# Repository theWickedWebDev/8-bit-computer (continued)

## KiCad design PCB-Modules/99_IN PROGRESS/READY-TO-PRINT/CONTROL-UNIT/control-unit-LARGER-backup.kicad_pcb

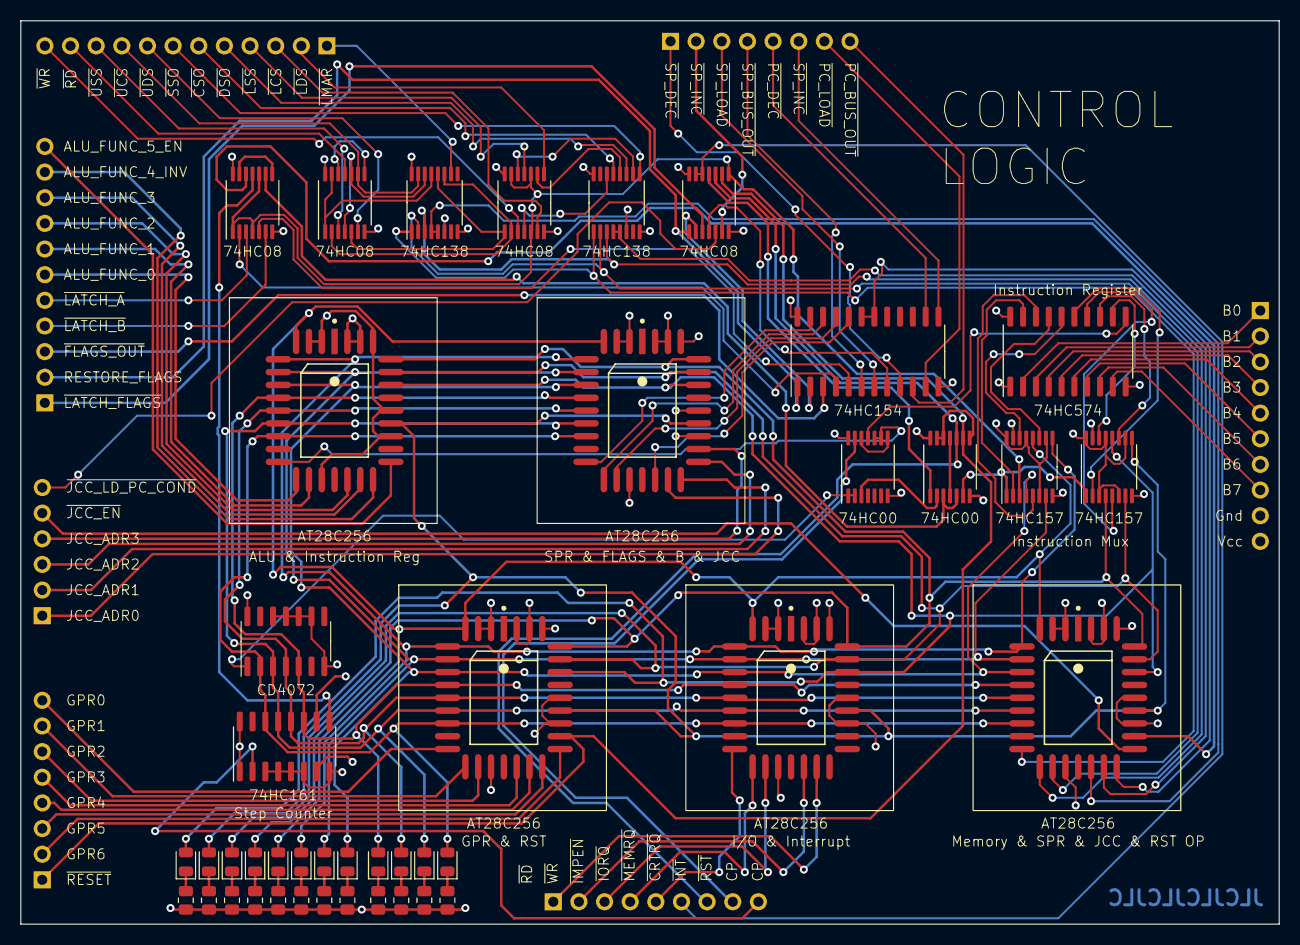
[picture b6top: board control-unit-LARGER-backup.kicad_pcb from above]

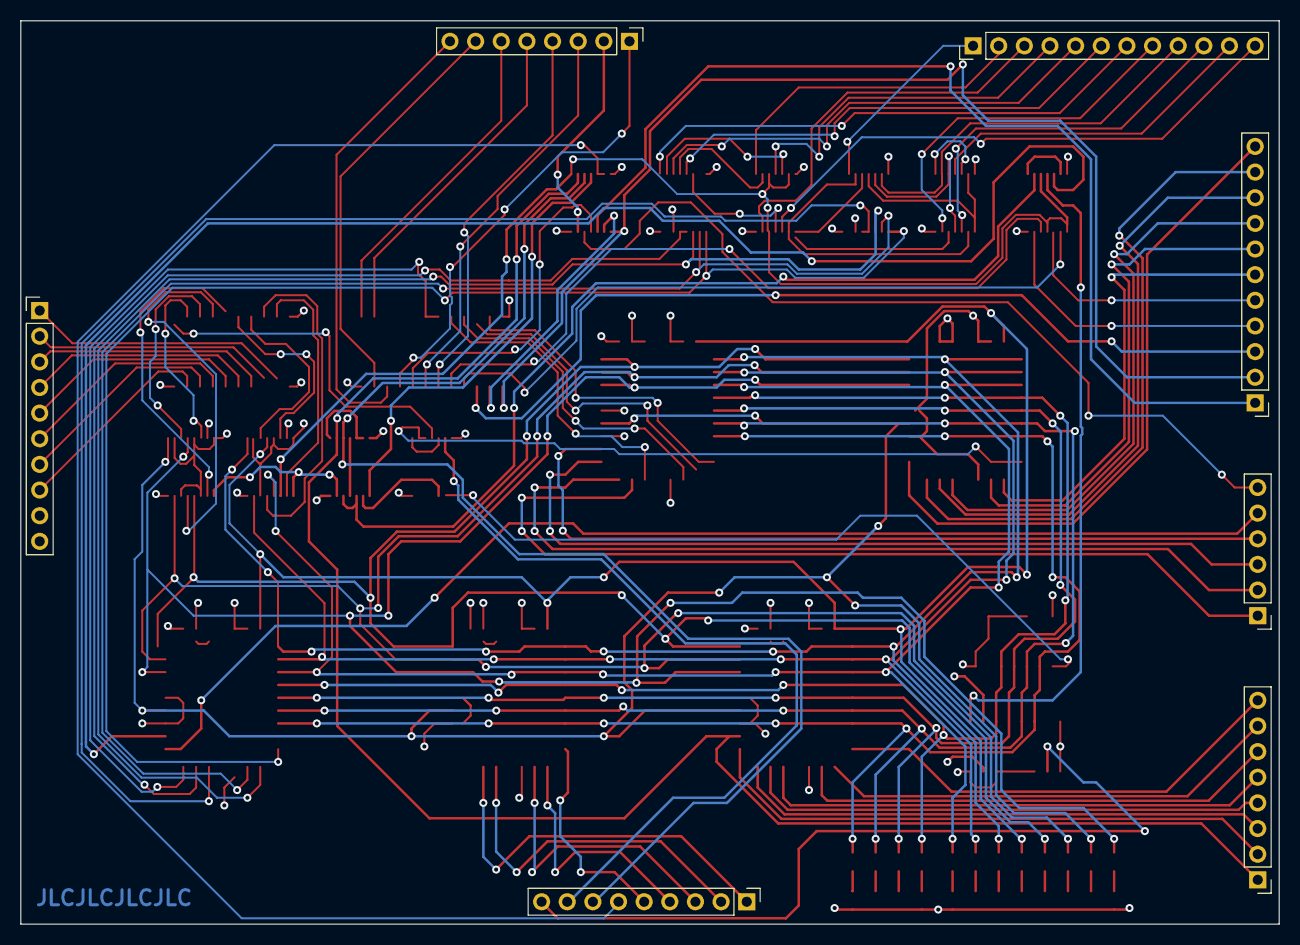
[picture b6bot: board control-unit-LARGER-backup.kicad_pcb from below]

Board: 4 copper layers, 124.6 x 89.5 mm, 50 parts (7 on the bottom side), 132 nets.

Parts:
D1, D2, D3, D4, D5, D6, D7, D8, D9, D10, D11, D12: LED; LED_0805_2012Metric
J1: Conn_01x09; PinHeader_1x09_P2.54mm_Vertical
J2, J7: Conn_01x08; PinHeader_1x08_P2.54mm_Vertical
J3: Conn_01x11; PinHeader_1x11_P2.54mm_Vertical
J4: Conn_01x10; PinHeader_1x10_P2.54mm_Vertical
J5: Conn_01x06; PinHeader_1x06_P2.54mm_Vertical
J6: Conn_01x12; PinHeader_1x12_P2.54mm_Vertical
R1, R2, R3, R4, R5, R6, R7, R8, R9, R10, R11, R12: R_US; R_0805_2012Metric
U1: 74LS161; SOIC-16_3.9x9.9mm_P1.27mm
U2: 4072; SOIC-14_3.9x8.7mm_P1.27mm
U3, U5: 74LS157; TSSOP-16_4.4x5mm_P0.65mm
U4, U19: 74LS00; TSSOP-14_4.4x5mm_P0.65mm
U6, U11, U12, U14, U15: PLCC32_28_28C256; Microchip-32J-10_2001-B-IPC_A
U7, U13: 74LS138; TSSOP-16_4.4x5mm_P0.65mm
U8: 74LS154; SO-24_5.3x15mm_P1.27mm
U9, U10, U16, U17: 74LS08; TSSOP-14_4.4x5mm_P0.65mm
U18: 74LS574; SO-20_5.3x12.6mm_P1.27mm

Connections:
/~RD_DATA: U7.14 (O1), U9.4, U9.10
/~RD_STACK: U7.13 (O2), U9.1, U9.13
/~WR_DATA: U7.12 (O3), U9.5, U17.1
/~WR_STACK: U7.11 (O4), U9.2, U17.2
ALU_FUNC_0: J3.6, U12.14 (I/O1)
ALU_FUNC_1: J3.7, U12.15 (I/O2)
ALU_FUNC_2: J3.8, U12.18 (I/O3)
ALU_FUNC_3: J3.9, U12.19 (I/O4)
ALU_FUNC_4: J3.10, U12.20 (I/O5)
ALU_FUNC_5_EN: J3.11, U12.21 (I/O6)
BUS0: J4.1, U18.2 (D0)
BUS1: J4.2, U18.3 (D1)
BUS2: J4.3, U18.4 (D2)
BUS3: J4.4, U18.5 (D3)
BUS4: J4.5, U18.6 (D4)
BUS5: J4.6, U18.7 (D5)
BUS6: J4.7, U18.8 (D6)
BUS7: J4.8, U18.9 (D7)
CLOCK: J1.8, U4.13
GND: J4.9, R1.2, R2.2, R3.2, R4.2, R5.2, R6.2, R7.2, R8.2, R9.2, R10.2, R11.2, R12.2, U1.3 (D0), U1.4 (D1), U1.5 (D2), U1.6 (D3), U1.8 (GND), U2.7 (VSS), U2.9, U2.10, U2.11, U2.12, U3.8 (GND), U3.15 (E), U4.7 (GND), U5.8 (GND), U5.15 (E), U6.2 (A14), U6.3 (A12), U6.16 (Gnd), U6.23 (~CE), U6.25 (~OE), U6.30 (A14), U7.8 (GND), U8.12 (GND), U9.7 (GND), U10.7 (GND), U11.2 (A14), U11.3 (A12), U11.16 (Gnd), U11.23 (~CE), U11.25 (~OE), U11.30 (A14), U12.2 (A14), U12.3 (A12), U12.16 (Gnd), U12.23 (~CE), U12.25 (~OE), U12.30 (A14), U13.8 (GND), U14.2 (A14), U14.3 (A12), U14.16 (Gnd), U14.23 (~CE), U14.25 (~OE), U14.30 (A14), U15.2 (A14), U15.3 (A12), U15.16 (Gnd), U15.23 (~CE), U15.25 (~OE), U15.30 (A14), U16.7 (GND), U17.7 (GND), U18.1 (OE), U18.10 (GND), U19.7 (GND)
GPR0: J2.8, U11.13 (I/O0)
GPR1: J2.7, U11.14 (I/O1)
GPR2: J2.6, U11.15 (I/O2)
GPR3: J2.5, U11.18 (I/O3)
GPR4: J2.4, U11.19 (I/O4)
GPR5: J2.3, U11.20 (I/O5)
GPR6: J2.2, U11.21 (I/O6)
INST0: D12.2 (A), U3.4 (Za), U6.7 (A4), U11.7 (A4), U12.7 (A4), U14.7 (A4), U15.7 (A4)
INST1: D11.2 (A), U3.7 (Zb), U6.6 (A5), U11.6 (A5), U12.6 (A5), U14.6 (A5), U15.6 (A5)
INST2: D10.2 (A), U3.9 (Zc), U6.5 (A6), U11.5 (A6), U12.5 (A6), U14.5 (A6), U15.5 (A6)
INST3: D9.2 (A), U3.12 (Zd), U6.4 (A7), U11.4 (A7), U12.4 (A7), U14.4 (A7), U15.4 (A7)
INST4: D8.2 (A), U5.4 (Za), U6.29 (A8), U11.29 (A8), U12.29 (A8), U14.29 (A8), U15.29 (A8)
INST5: D7.2 (A), U5.7 (Zb), U6.28 (A9), U11.28 (A9), U12.28 (A9), U14.28 (A9), U15.28 (A9)
INST6: D6.2 (A), U5.9 (Zc), U6.24 (A10), U11.24 (A10), U12.24 (A10), U14.24 (A10), U15.24 (A10)
INST7: D5.2 (A), U5.12 (Zd), U6.27 (A11), U11.27 (A11), U12.27 (A11), U14.27 (A11), U15.27 (A11)
INSTRUCTION_0: U3.2 (I0a), U18.19 (Q0)
INSTRUCTION_1: U3.5 (I0b), U18.18 (Q1)
INSTRUCTION_2: U3.11 (I0c), U18.17 (Q2)
INSTRUCTION_3: U3.14 (I0d), U18.16 (Q3)
INSTRUCTION_4: U5.2 (I0a), U18.15 (Q4)
INSTRUCTION_5: U5.5 (I0b), U18.14 (Q5)
INSTRUCTION_6: U5.11 (I0c), U18.13 (Q6)
INSTRUCTION_7: U5.14 (I0d), U18.12 (Q7)
JCC_ADR0: J5.1, U14.19 (I/O4)
JCC_ADR1: J5.2, U14.20 (I/O5)
JCC_ADR2: J5.3, U14.21 (I/O6)
JCC_ADR3: J5.4, U14.22 (I/O7)
JCC_LD_PC_COND: J5.6, U10.5
MEM0: U6.13 (I/O0), U7.1 (A0), U13.1 (A0)
MEM1: U6.15 (I/O2), U7.2 (A1), U13.2 (A1)
MEM2: U6.14 (I/O1), U7.3 (A2), U13.3 (A2)
unnamed: D1.1 (K), R1.1
unnamed: D2.1 (K), R2.1
unnamed: D3.1 (K), R3.1
unnamed: D4.1 (K), R4.1
unnamed: D5.1 (K), R5.1
unnamed: D6.1 (K), R6.1
unnamed: D7.1 (K), R7.1
unnamed: D8.1 (K), R8.1
unnamed: D9.1 (K), R9.1
unnamed: D10.1 (K), R10.1
unnamed: D11.1 (K), R11.1
unnamed: D12.1 (K), R12.1
unnamed: U1.9 (~PE), U16.11
unnamed: U2.1, U4.1, U4.2
unnamed: U4.8, U4.12
unnamed: U9.8, U9.12
unnamed: U8.2 (S1), U10.2
unnamed: U8.8 (S7), U10.4
unnamed: U10.11, U19.1
unnamed: U13.10 (O5), U17.12
unnamed: U13.12 (O3), U17.9
unnamed: U13.14 (O1), U17.4
unnamed: U8.4 (S3), U16.2
unnamed: U8.5 (S4), U16.5
unnamed: U4.11, U18.11 (Cp)
unnamed: U4.3, U19.2
unnamed: U3.1 (S), U5.1 (S), U19.6
unnamed: U19.4, U19.11
unnamed: U19.8, U19.12, U19.13
RESTORE_FLAGS: J3.2, U8.1 (S0), U10.1
SPR_FLAGS_ACC_B_CNTL_0: U8.23 (A0), U14.13 (I/O0)
SPR_FLAGS_ACC_B_CNTL_1: U8.22 (A1), U14.14 (I/O1)
SPR_FLAGS_ACC_B_CNTL_2: U8.21 (A2), U14.15 (I/O2)
SPR_FLAGS_ACC_B_CNTL_3: U8.20 (A3), U14.18 (I/O3)
STEP0: D4.2 (A), U1.14 (Q0), U2.2, U6.11 (A0), U11.11 (A0), U12.11 (A0), U14.11 (A0), U15.11 (A0)
STEP1: D3.2 (A), U1.13 (Q1), U2.3, U6.10 (A1), U11.10 (A1), U12.10 (A1), U14.10 (A1), U15.10 (A1)
STEP2: D2.2 (A), U1.12 (Q2), U2.4, U6.9 (A2), U11.9 (A2), U12.9 (A2), U14.9 (A2), U15.9 (A2)
STEP3: D1.2 (A), U1.11 (Q3), U2.5, U6.8 (A3), U11.8 (A3), U12.8 (A3), U14.8 (A3), U15.8 (A3)
VCC: J4.10, U1.1 (~MR), U1.7 (CEP), U1.10 (CET), U1.16 (VCC), U2.14 (VDD), U3.6 (I1b), U3.10 (I1c), U3.13 (I1d), U3.16 (VCC), U4.14 (VCC), U5.3 (I1a), U5.6 (I1b), U5.10 (I1c), U5.13 (I1d), U5.16 (VCC), U6.31 (~WE), U6.32 (Vcc), U7.6 (E3), U7.16 (VCC), U8.24 (VCC), U9.14 (VCC), U10.14 (VCC), U11.31 (~WE), U11.32 (Vcc), U12.31 (~WE), U12.32 (Vcc), U13.6 (E3), U13.16 (VCC), U14.31 (~WE), U14.32 (Vcc), U15.31 (~WE), U15.32 (Vcc), U16.14 (VCC), U17.14 (VCC), U18.20 (VCC), U19.14 (VCC)
~CLOCK: J1.9, U1.2 (CP)
~CODE_SEGMENT_OUT: J6.6, U13.13 (O2)
~CPU_INTERRUPT: J1.6, U10.12, U10.13
~DATA_SEGMENT_OUT: J6.5, U13.11 (O4)
~FLAGS_OUT: J3.3, U8.3 (S2)
~INSTRUCTION_REG_IN: U4.9, U4.10, U12.13 (I/O0)
~INTERRUPT_HANDLER_EN: U16.9, U19.3, U19.5
~IO_REQUEST: J1.4, U15.14 (I/O1)
~IRQ_MASK_PORT_EN: J1.3, U15.15 (I/O2)
~JCC_EN: J5.5, U6.21 (I/O6)
~LATCH_ACCUMULATOR: J3.5, U16.3
~LATCH_B: J3.4, U16.6
~LATCH_CODE_SEGMENT: J6.3, U17.6
~LATCH_DATA_SEGMENT: J6.2, U17.8
~LATCH_FLAGS: J3.1, U10.3
~LATCH_MAR: J6.1, U7.10 (O5)
~LATCH_STACK_SEGMENT: J6.4, U17.11
~MEMORY_ENABLE: U6.18 (I/O3), U7.4 (E1), U7.5 (E2)
~MEM_READ: J6.11, U9.11
~MEM_REQ: J1.5, U15.13 (I/O0)
~MEM_WRITE: J6.12, U17.3
~PC_BUS_OUT: J7.1, U8.9 (S8)
~PC_DEC: J7.4, U8.6 (S5)
~PC_INC: J7.3, U8.7 (S6)
~PC_LOAD: J7.2, U10.6
~READ: J1.1, U15.19 (I/O4)
~RESET_IN: J1.7, U10.10, U19.10
~RESET_STEP_COUNTER: U6.22 (I/O7), U16.12
~RESET: U3.3 (I1a), U10.8, U16.1, U16.4, U16.10, U17.5, U17.10, U17.13
~SEGMENT_REGISTER_EN: U6.19 (I/O4), U13.4 (E1), U13.5 (E2)
~SOFTWARE_RESET: J2.1, U10.9, U11.22 (I/O7), U19.9
~SPR_FLAGS_ACC_B_EN: U6.20 (I/O5), U8.18 (E0), U8.19 (E1)
~SP_BUS_OUT: J7.5, U8.14 (S12)
~SP_DEC: J7.8, U8.10 (S9)
~SP_INC: J7.7, U8.11 (S10)
~SP_LOAD: J7.6, U8.13 (S11)
~STACK_SEGMENT_OUT: J6.7, U13.9 (O6)
~TRIGGER_RESET_STEP: U16.8, U16.13
~USE_CODE_SEGMENT: J6.9, U7.15 (O0), U9.9
~USE_DATA_SEGMENT: J6.8, U9.6
~USE_STACK_SEGMENT: J6.10, U9.3
~WRITE: J1.2, U15.18 (I/O3)

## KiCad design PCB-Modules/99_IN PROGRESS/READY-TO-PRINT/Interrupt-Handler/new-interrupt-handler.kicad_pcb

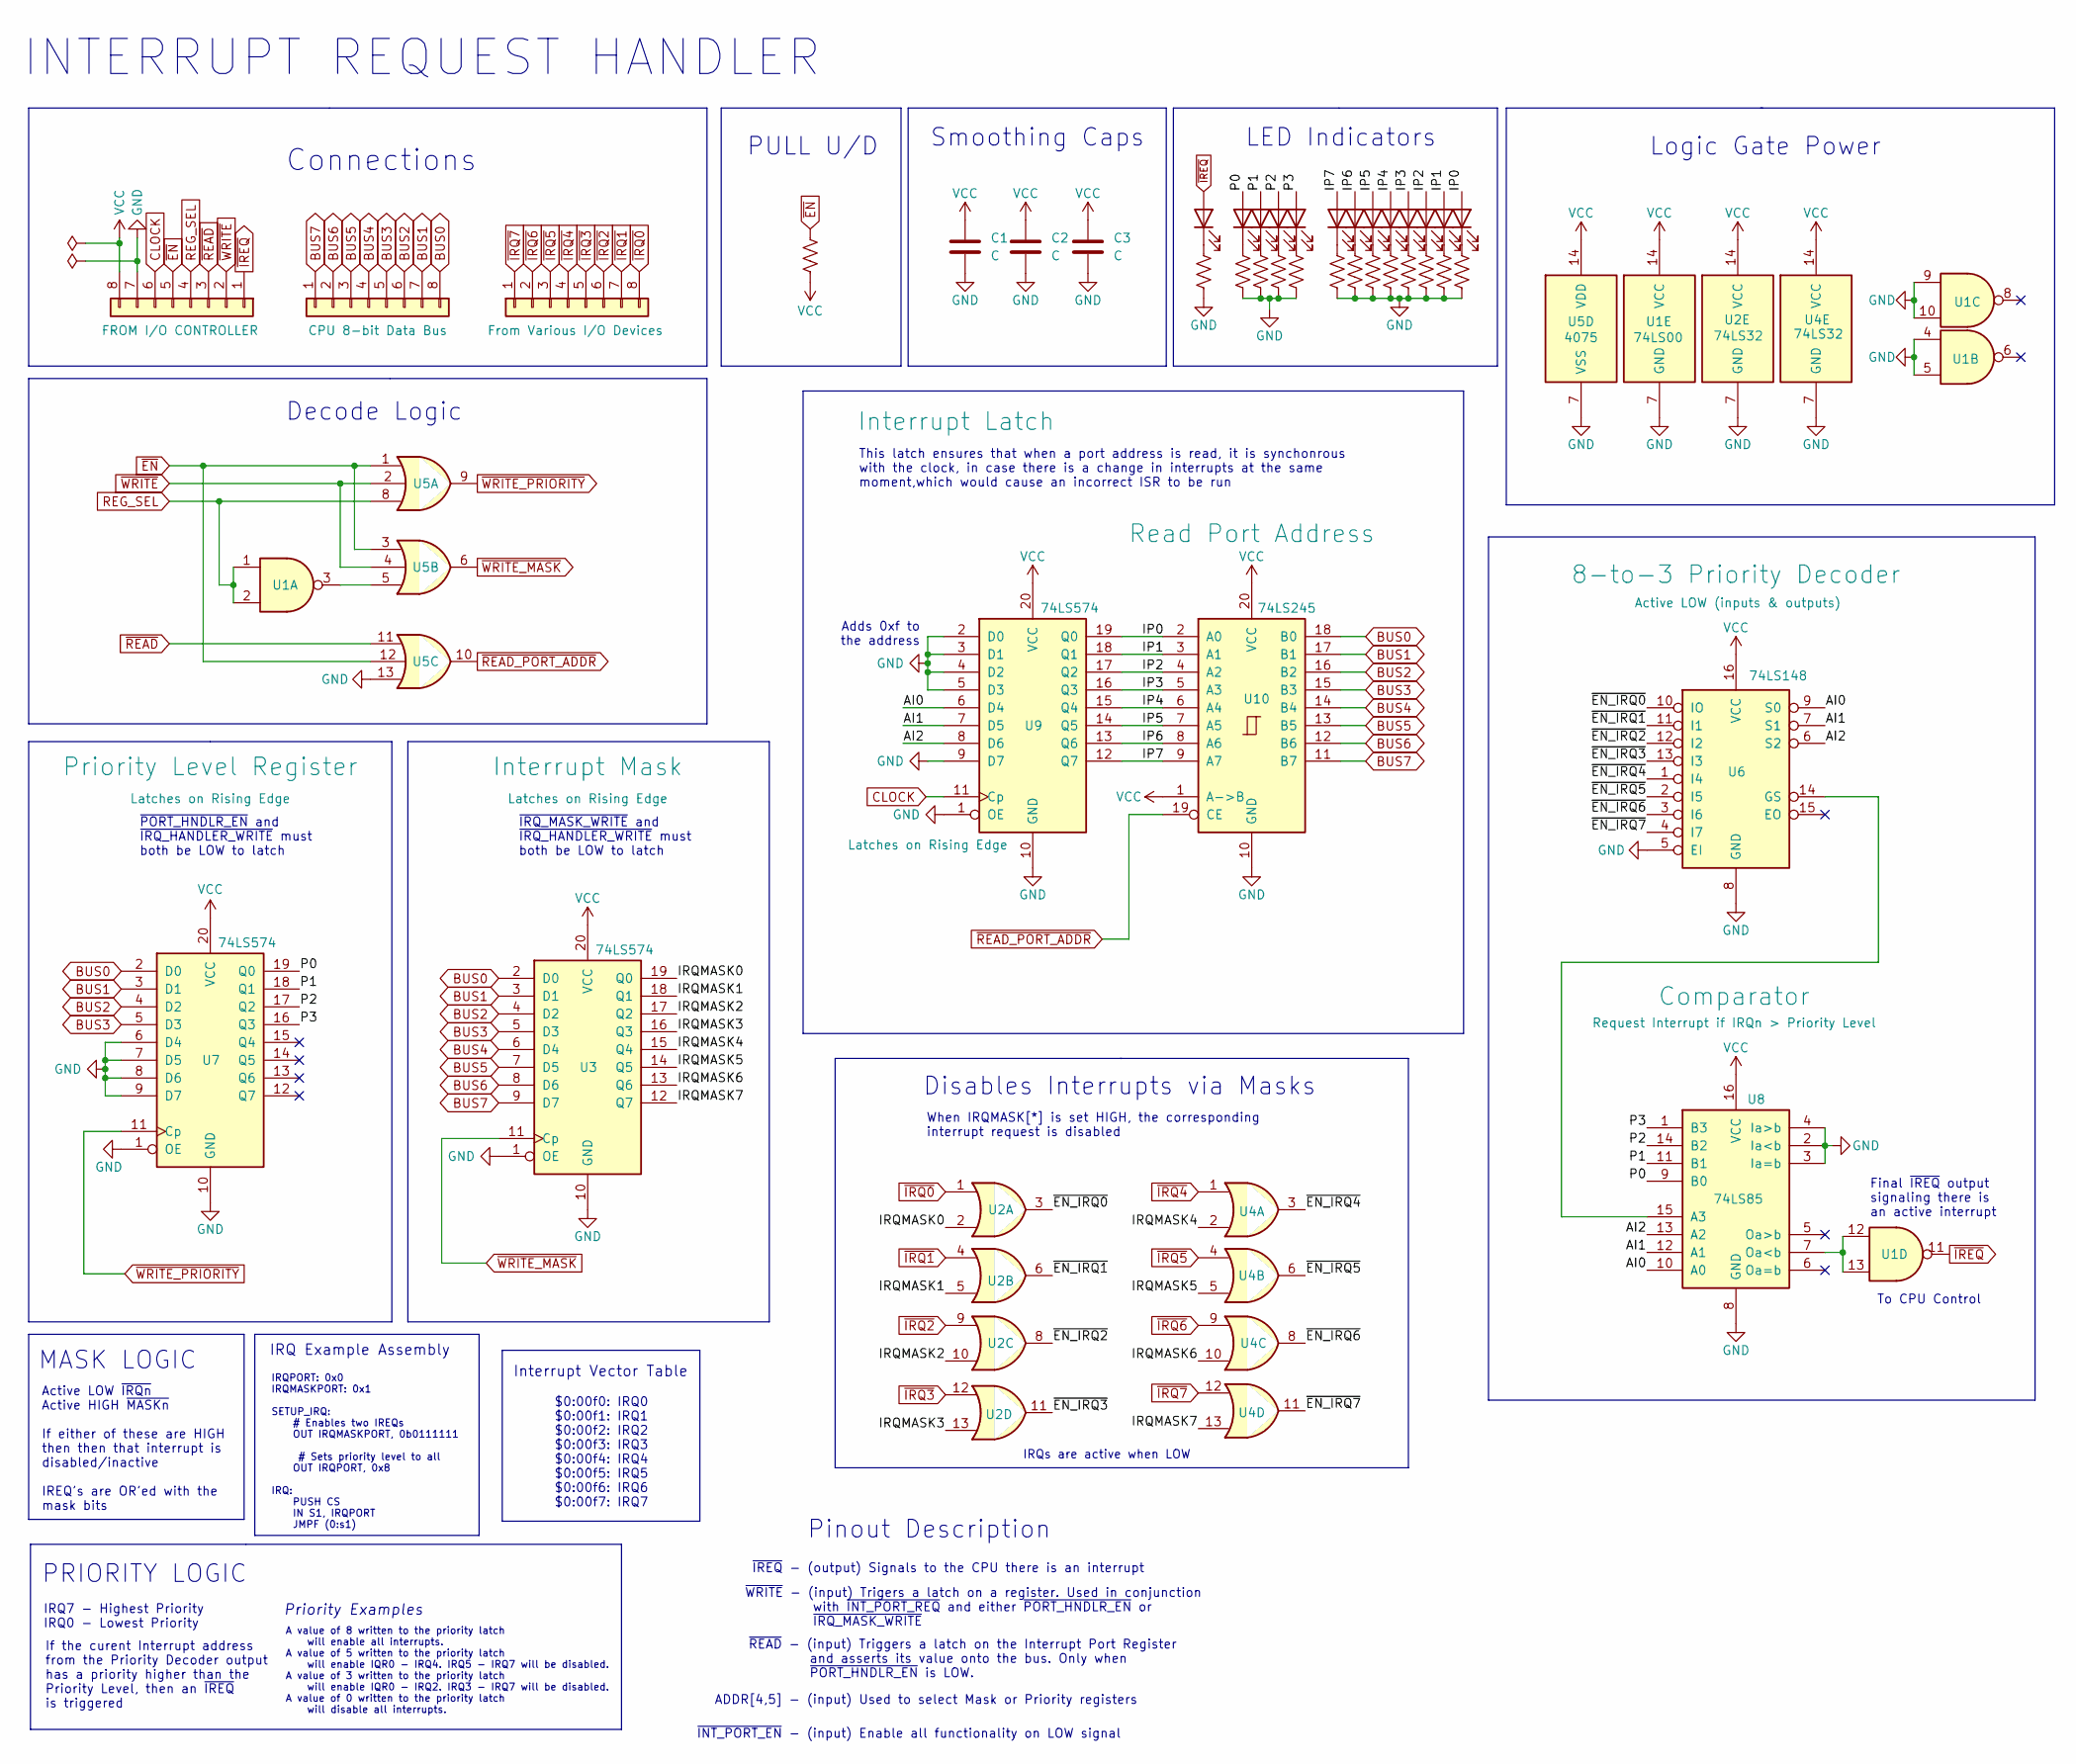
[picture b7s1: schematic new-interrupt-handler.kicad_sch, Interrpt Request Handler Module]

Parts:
C1, C2, C3: C; C_0805_2012Metric
D1, D2, D3, D4, D5, D6, D7, D8, D9, D10, D11, D12, D13: LED; LED_0805_2012Metric
J1, J2, J3: Conn_01x08; PinHeader_1x08_P2.54mm_Vertical
R1, R2, R3, R4, R5, R6, R7, R8, R9, R10, R11, R12, R13, R14: R_US; R_0805_2012Metric
U1: 74LS00; TSSOP-14_4.4x5mm_P0.65mm
U2, U4: 74LS32; TSSOP-14_4.4x5mm_P0.65mm
U3, U7, U9: 74LS574; SO-20_5.3x12.6mm_P1.27mm
U5: 4075
U6: 74LS148; SOIC-16_4.55x10.3mm_P1.27mm
U8: 74LS85; SOIC-16_4.55x10.3mm_P1.27mm
U10: 74LS245; TSSOP-20_4.4x6.5mm_P0.65mm

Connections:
/AI0: U6.9 (S0), U8.10 (A0), U9.6 (D4)
/AI1: U6.7 (S1), U8.12 (A1), U9.7 (D5)
/AI2: U6.6 (S2), U8.13 (A2), U9.8 (D6)
/IP0: D13.2 (A), U9.19 (Q0), U10.2 (A0)
/IP1: D12.2 (A), U9.18 (Q1), U10.3 (A1)
/IP2: D11.2 (A), U9.17 (Q2), U10.4 (A2)
/IP3: D10.2 (A), U9.16 (Q3), U10.5 (A3)
/IP4: D9.2 (A), U9.15 (Q4), U10.6 (A4)
/IP5: D8.2 (A), U9.14 (Q5), U10.7 (A5)
/IP6: D7.2 (A), U9.13 (Q6), U10.8 (A6)
/IP7: D6.2 (A), U9.12 (Q7), U10.9 (A7)
/IRQMASK0: U2.2, U3.19 (Q0)
/IRQMASK1: U2.5, U3.18 (Q1)
/IRQMASK2: U2.10, U3.17 (Q2)
/IRQMASK3: U2.13, U3.16 (Q3)
/IRQMASK4: U3.15 (Q4), U4.2
/IRQMASK5: U3.14 (Q5), U4.5
/IRQMASK6: U3.13 (Q6), U4.10
/IRQMASK7: U3.12 (Q7), U4.13
/P0: D2.2 (A), U7.19 (Q0), U8.9 (B0)
/P1: D3.2 (A), U7.18 (Q1), U8.11 (B1)
/P2: D4.2 (A), U7.17 (Q2), U8.14 (B2)
/P3: D5.2 (A), U7.16 (Q3), U8.1 (B3)
/~EN_IRQ0: U2.3, U6.10 (IO)
/~EN_IRQ1: U2.6, U6.11 (I1)
/~EN_IRQ2: U2.8, U6.12 (I2)
/~EN_IRQ3: U2.11, U6.13 (I3)
/~EN_IRQ4: U4.3, U6.1 (I4)
/~EN_IRQ5: U4.6, U6.2 (I5)
/~EN_IRQ6: U4.8, U6.3 (I6)
/~EN_IRQ7: U4.11, U6.4 (I7)
BUS0: J2.8, U3.2 (D0), U7.2 (D0), U10.18 (B0)
BUS1: J2.7, U3.3 (D1), U7.3 (D1), U10.17 (B1)
BUS2: J2.6, U3.4 (D2), U7.4 (D2), U10.16 (B2)
BUS3: J2.5, U3.5 (D3), U7.5 (D3), U10.15 (B3)
BUS4: J2.4, U3.6 (D4), U10.14 (B4)
BUS5: J2.3, U3.7 (D5), U10.13 (B5)
BUS6: J2.2, U3.8 (D6), U10.12 (B6)
BUS7: J2.1, U3.9 (D7), U10.11 (B7)
CLOCK: J1.6, U9.11 (Cp)
GND: C1.2, C2.2, C3.2, J1.7, R1.2, R2.2, R3.2, R4.2, R5.2, R6.2, R7.2, R8.2, R9.2, R10.2, R11.2, R12.2, R13.2, U1.4, U1.5, U1.7 (GND), U1.9, U1.10, U2.7 (GND), U3.1 (OE), U3.10 (GND), U4.7 (GND), U5.7 (VSS), U5.13, U6.5 (EI), U6.8 (GND), U7.1 (OE), U7.6 (D4), U7.7 (D5), U7.8 (D6), U7.9 (D7), U7.10 (GND), U8.2 (Ia<b), U8.3 (Ia=b), U8.4 (Ia>b), U8.8 (GND), U9.1 (OE), U9.2 (D0), U9.3 (D1), U9.4 (D2), U9.5 (D3), U9.9 (D7), U9.10 (GND), U10.10 (GND)
unnamed: D1.1 (K), R1.1
unnamed: D2.1 (K), R2.1
unnamed: D3.1 (K), R3.1
unnamed: D4.1 (K), R4.1
unnamed: D5.1 (K), R5.1
unnamed: D6.1 (K), R6.1
unnamed: D7.1 (K), R7.1
unnamed: D8.1 (K), R8.1
unnamed: D9.1 (K), R9.1
unnamed: D10.1 (K), R10.1
unnamed: D11.1 (K), R11.1
unnamed: D12.1 (K), R12.1
unnamed: D13.1 (K), R13.1
unnamed: U1.3, U5.5
unnamed: U1.12, U1.13, U8.7 (Oa<b)
unnamed: U6.14 (GS), U8.15 (A3)
REG_SEL: J1.4, U1.1, U1.2, U5.8
VCC: C1.1, C2.1, C3.1, J1.8, R14.2, U1.14 (VCC), U2.14 (VCC), U3.20 (VCC), U4.14 (VCC), U5.14 (VDD), U6.16 (VCC), U7.20 (VCC), U8.16 (VCC), U9.20 (VCC), U10.1 (A->B), U10.20 (VCC)
~EN: J1.5, R14.1, U5.1, U5.3, U5.12
~IREQ: D1.2 (A), J1.1, U1.11
~IRQ0: J3.8, U2.1
~IRQ1: J3.7, U2.4
~IRQ2: J3.6, U2.9
~IRQ3: J3.5, U2.12
~IRQ4: J3.4, U4.1
~IRQ5: J3.3, U4.4
~IRQ6: J3.2, U4.9
~IRQ7: J3.1, U4.12
~READ_PORT_ADDR: U5.10, U10.19 (CE)
~READ: J1.3, U5.11
~WRITE_MASK: U3.11 (Cp), U5.6
~WRITE_PRIORITY: U5.9, U7.11 (Cp)
~WRITE: J1.2, U5.2, U5.4

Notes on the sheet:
When IRQMASK[*] is set HIGH, the corresponding interrupt request is disabled
Disables Interrupts via Masks
IRQPORT: 0x0 IRQMASKPORT: 0x1 SETUP_IRQ: # Enables two IREQs OUT IRQMASKPORT, 0b0111111 # Sets priority level to all OUT IRQPORT, 0x8 IRQ: PUSH CS IN S1, IRQPORT JMPF (0:s1)
~{IRQ_MASK_WRITE} and ~{IRQ_HANDLER_WRITE} must both be LOW to latch
INTERRUPT REQUEST HANDLER
~{INT_PORT_EN} - (input) Enable all functionality on LOW signal
Pinout Description
LED Indicators
To CPU Control
IRQs are active when LOW
PULL U/D
$0:00f0: IRQ0 $0:00f1: IRQ1 $0:00f2: IRQ2 $0:00f3: IRQ3 $0:00f4: IRQ4 $0:00f5: IRQ5 $0:00f6: IRQ6 $0:00f7: IRQ7
~{WRITE} - (input) Trigers a latch on a register. Used in conjunction with ~{INT_PORT_REQ} and either ~{PORT_HNDLR_EN} or ~{IRQ_MASK_WRITE}
Logic Gate Power
~{IREQ} - (output) Signals to the CPU there is an interrupt
IRQ7 - Highest Priority IRQ0 - Lowest Priority
If the curent Interrupt address from the Priority Decoder output has a priority higher than the Priority Level, then an ~{IREQ} is triggered
Adds 0xf to the address
A value of 8 written to the priority latch will enable all interrupts. A value of 5 written to the priority latch will enable IQR0 - IRQ4. IRQ5 - IRQ7 will be disabled. A value of 3 written to the priority latch will enable IQR0 - IRQ2. IRQ3 - IRQ7 will be disabled. A value of 0 written to the prio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
Active LOW ~{IRQn} Active HIGH ~{MASKn} If either of these are HIGH then then that interrupt is disabled/inactive IREQ's are OR'ed with the mask bits
ADDR[4,5] - (input) Used to select Mask or Priority registers
MASK LOGIC
This latch ensures that when a port address is read, it is synchonrous with the clock, in case there is a change in interrupts at the same moment,which would cause an incorrect ISR to be run
Smoothing Caps
IRQ Example Assembly
Final ~{IREQ} output signaling there is an active interrupt
Priority Examples
~{PORT_HNDLR_EN} and ~{IRQ_HANDLER_WRITE} must both be LOW to latch
PRIORITY LOGIC
Decode Logic
~{READ} - (input) Triggers a latch on the Interrupt Port Register and asserts its value onto the bus. Only when ~{PORT_HNDLR_EN} is LOW.
Connections
Interrupt Vector Table

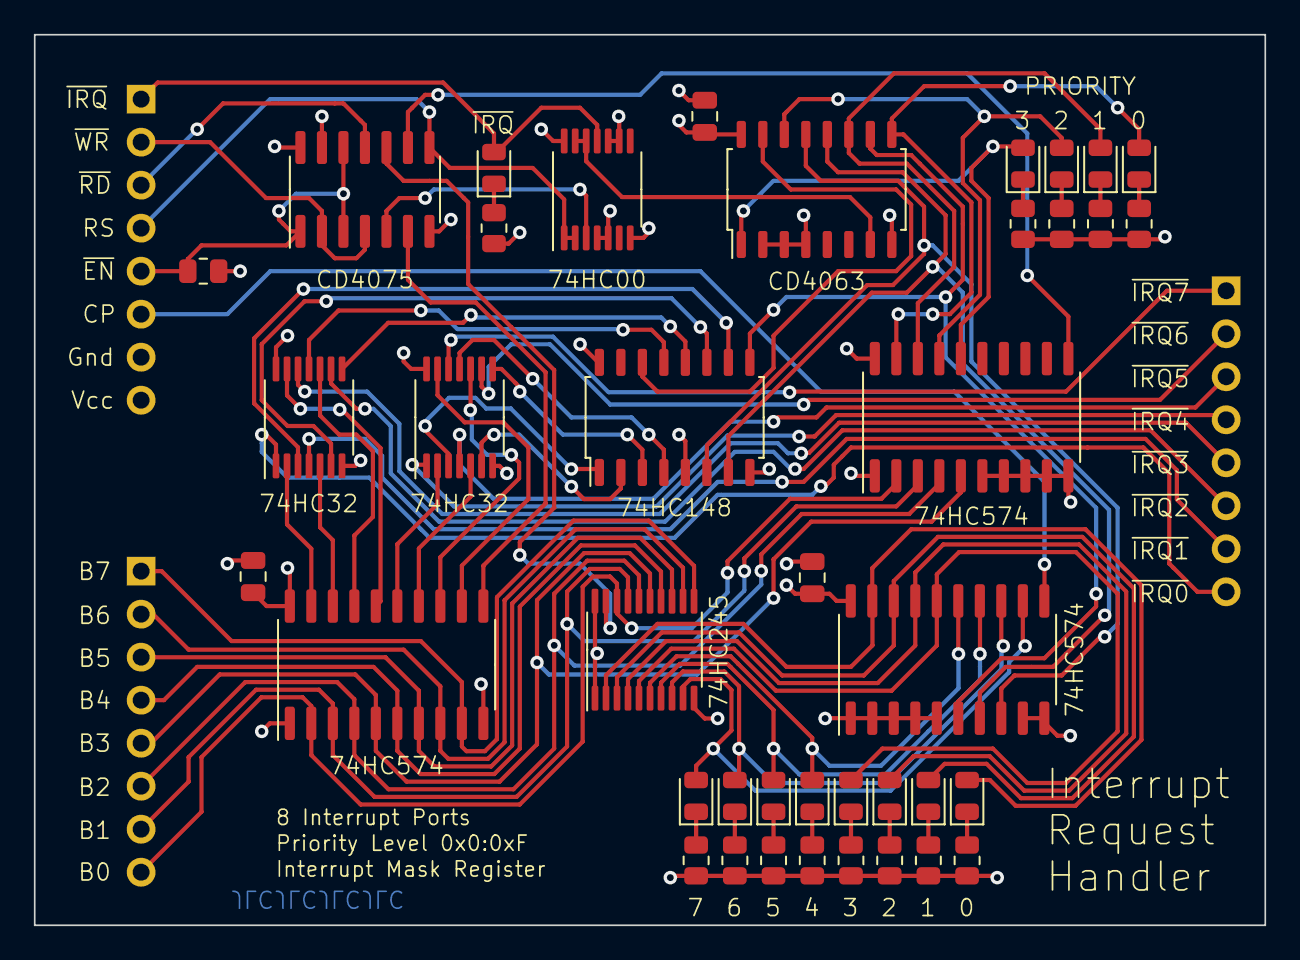
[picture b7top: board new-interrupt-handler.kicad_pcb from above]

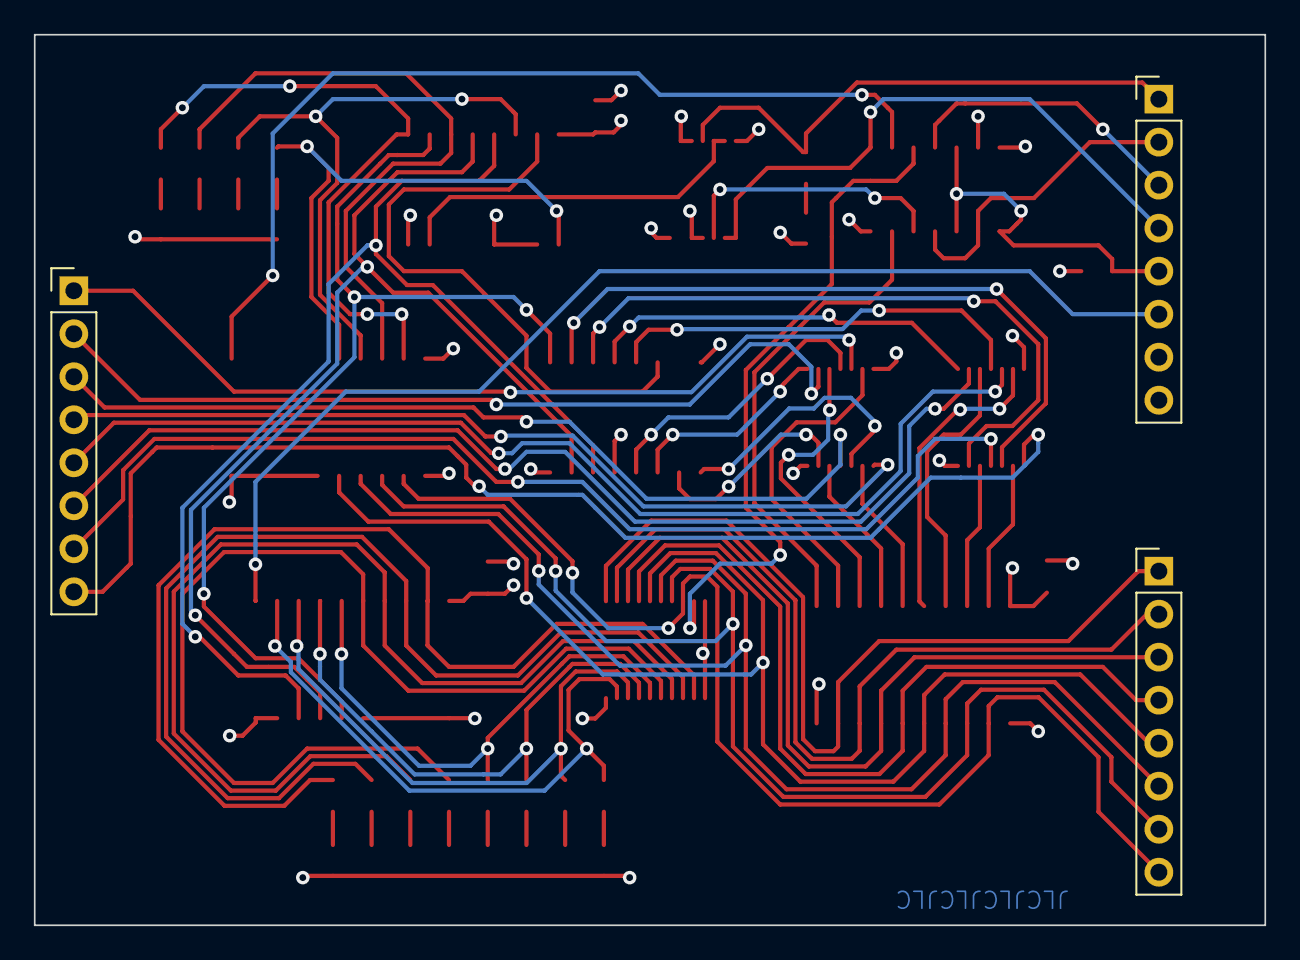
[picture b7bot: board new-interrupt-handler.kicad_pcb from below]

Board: 4 copper layers, 72.7 x 52.6 mm, 43 parts (3 on the bottom side), 74 nets.
